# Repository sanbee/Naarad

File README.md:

# Naarad
A simple house monitor and control system. 

The *Naarad* system is a network of remote Nodes with a radio operating
in the [ISM band](https://en.wikipedia.org/wiki/ISM_band) and a Base
Station with an [RFM69CW](http://www.hoperf.com/rf_transceiver/modules/RFM69CW.html) (RFM) packet radio, currently connected to an
Arduino UNO.  The UNO talks to a Linux-based computer (currently a
Raspberry PI (RPi)) via the serial connection.  The RPi also listens
for incoming socket connections.  Commands for the *Naarad* network
are either generated at the RPi or arrive at the socket (e.g. from a
remotely connected device).  Commands meant for the UNO or the remote
Nodes are sent to the UNO via the serial connection.  The server on
the UNO then transmits the commands for the remote Nodes via the RFM
or via another radio for remote [OOK](https://en.wikipedia.org/wiki/On-off_keying)
devices.  Similarly, information from remote Nodes is received at the 
UNO via the RFM and immediately transferred to the RPi for consumption 
via the serial connection. The block level system diagram looks like this:

This repository has the code for the three components of the Naarad system: 
  * The code running on the MCUs on the remote nodes is in the [Nodes](Nodes) directory
  * The code running on the Arduino UNO on the Base Station is in the [BaseStation](BaseStation) directory
  * The code running on the central socket server (Raspberry Pi) is in the [RPi](RPi) directory

### Resources
The communication with the RFM is done using the
[JeeLib](https://github.com/jcw/jeelib) library from
[JeeLabs](https://jeelabs.org).

The communication hardware on the remote Nodes is derived from the
[TinyTx](https://nathan.chantrell.net/tinytx-wireless-sensor) design.
For programming the ATTiny84 using an Arduino, I followed the
instructions from [here](https://nathan.chantrell.net/20120225/an-attiny-based-wireless-temperature-sensor/).

[This](http://www.gammon.com.au/power) article by [Nick Gammon](http://www.gammon.com.au/forum/bbshowbio.php?bbuser_id=1) is an excellent resource for techniques to reduce power consumption on MCU. While the code here is for Arduino (Atmega328P), some of the techniques apply to other Atmel processors.  A similar article sepecifically for ATTiny84 would be great.  This also has a post with very useful information about batteries (including self-drainage rates etc.).

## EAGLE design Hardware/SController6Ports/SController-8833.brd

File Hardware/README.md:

# Naarad Hardware

|  Prototype | Version 1 |
| :---:     | :---:   |
|   |   |

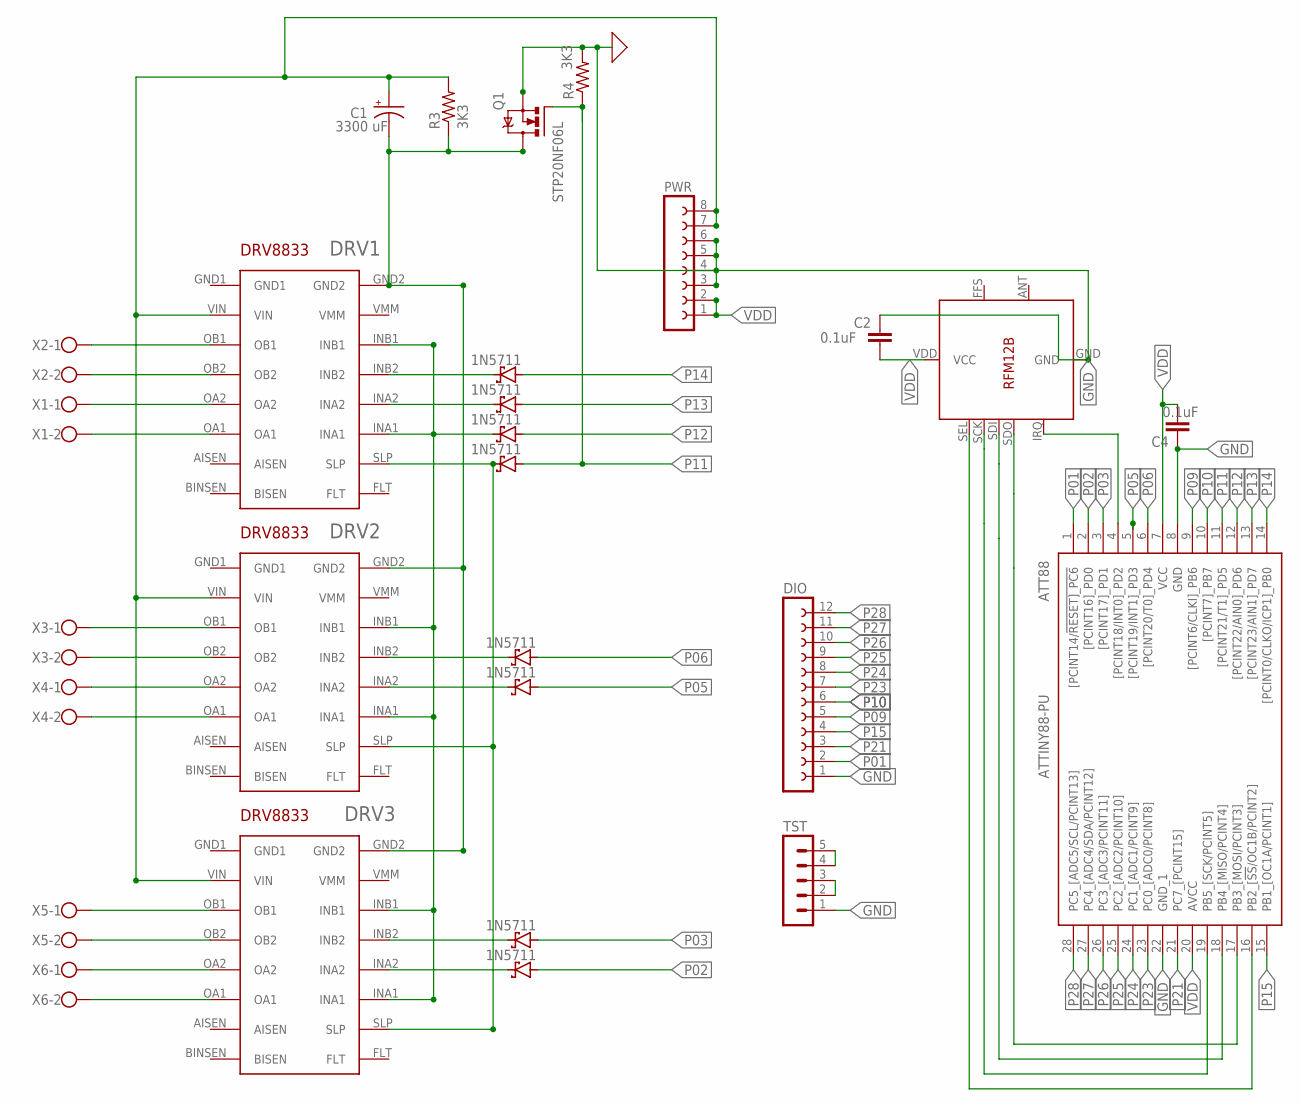
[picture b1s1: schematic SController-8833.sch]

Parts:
1: DRV1; POLOLU-DRV8833
2: DRV2; POLOLU-DRV8833
3: DRV3; POLOLU-DRV8833
ATT88: ATTINY88-PU; DIP794W53P254L3467H457Q28N
C1: 3300 uF; E5-10,5
C2, C4: 0.1uF; C2.5-2
D1, D2, D3, D4, D5, D6, D7, D8: 1N5711; F126Z12
DIO: FE12-1; FE12
PWR: FE08-1; FE08
Q1: STP20NF06L; TO220BV
R3, R4: 3K3; 0204/7
RFM69CW: RFM69CW; RFM12B
TST: MA05-1
X1, X2, X3, X4, X5, X6: W237-102

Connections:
CMN1: 1.INA1, 1.INB1, 2.INA1, 2.INB1, 3.INA1, 3.INB1, D3.C
GND: ATT88.8 (GND), ATT88.22 (GND_1), C2.2, C4.1, DIO.1, PWR.3, PWR.4, PWR.5, PWR.6, Q1.S, R4.2, RFM69CW.GND, TST.1
IRQ: ATT88.4 ([PCINT18/INT0]_PD2), RFM69CW.IRQ
unnamed: 2.INB2, D5.C
unnamed: 1.INB2, D1.C
unnamed: TST.4, TST.5
unnamed: TST.2, TST.3
unnamed: 1.INA2, D2.C
unnamed: 3.INB2, D7.C
unnamed: 2.INA2, D6.C
unnamed: 3.INA2, D8.C
OA11: 1.OA1, X1.2
OA12: 2.OA1, X4.2
OA13: 3.OA1, X6.2
OA21: 1.OA2, X1.1
OA22: 2.OA2, X4.1
OA23: 3.OA2, X6.1
OB11: 1.OB1, X2.1
OB12: 2.OB1, X3.1
OB13: 3.OB1, X5.1
OB21: 1.OB2, X2.2
OB22: 2.OB2, X3.2
OB23: 3.OB2, X5.2
P01: ATT88.1 ([PCINT14/!RESET]_PC6), DIO.2
P02: ATT88.2 ([PCINT16]_PD0), D8.A
P03: ATT88.3 ([PCINT17]_PD1), D7.A
P05: ATT88.5 ([PCINT19/INT1]_PD3), D6.A
P06: ATT88.6 ([PCINT20/T0]_PD4), D5.A
P09: ATT88.9 ([PCINT6/CLKI]_PB6), DIO.5
P10: ATT88.10 ([PCINT7]_PB7), DIO.6
P11: ATT88.11 ([PCINT21/T1]_PD5), D4.A, Q1.G, R4.1
P12: ATT88.12 ([PCINT22/AIN0]_PD6), D3.A
P13: ATT88.13 ([PCINT23/AIN1]_PD7), D2.A
P14: ATT88.14 ([PCINT0/CLKO/ICP1]_PB0), D1.A
P15: ATT88.15 (PB1_[OC1A/PCINT1]), DIO.4
P21: ATT88.21 (PC7_[PCINT15]), DIO.3
P23: ATT88.23 (PC0_[ADC0/PCINT8]), DIO.7
P24: ATT88.24 (PC1_[ADC1/PCINT9]), DIO.8
P25: ATT88.25 (PC2_[ADC2/PCINT10]), DIO.9
P26: ATT88.26 (PC3_[ADC3/PCINT11]), DIO.10
P27: ATT88.27 (PC4_[ADC4/SDA/PCINT12]), DIO.11
P28: ATT88.28 (PC5_[ADC5/SCL/PCINT13]), DIO.12
SCK: ATT88.19 (PB5_[SCK/PCINT5]), RFM69CW.SCK
SDI: ATT88.18 (PB4_[MISO/PCINT4]), RFM69CW.SDI
SDO: ATT88.17 (PB3_[MOSI/PCINT3]), RFM69CW.SDO
SEL: ATT88.16 (PB2_[!SS!/OC1B/PCINT2]), RFM69CW.SEL
SLP: 1.SLP, 2.SLP, 3.SLP, D4.C
VDD: ATT88.7 (VCC), ATT88.20 (AVCC), C2.1, C4.2, PWR.1, PWR.2, RFM69CW.VDD (VCC)
VGND: 1.GND2, 2.GND2, 3.GND2, C1.-, Q1.D, R3.1
VIN: 1.VIN, 2.VIN, 3.VIN, C1.+, PWR.7, PWR.8, R3.2

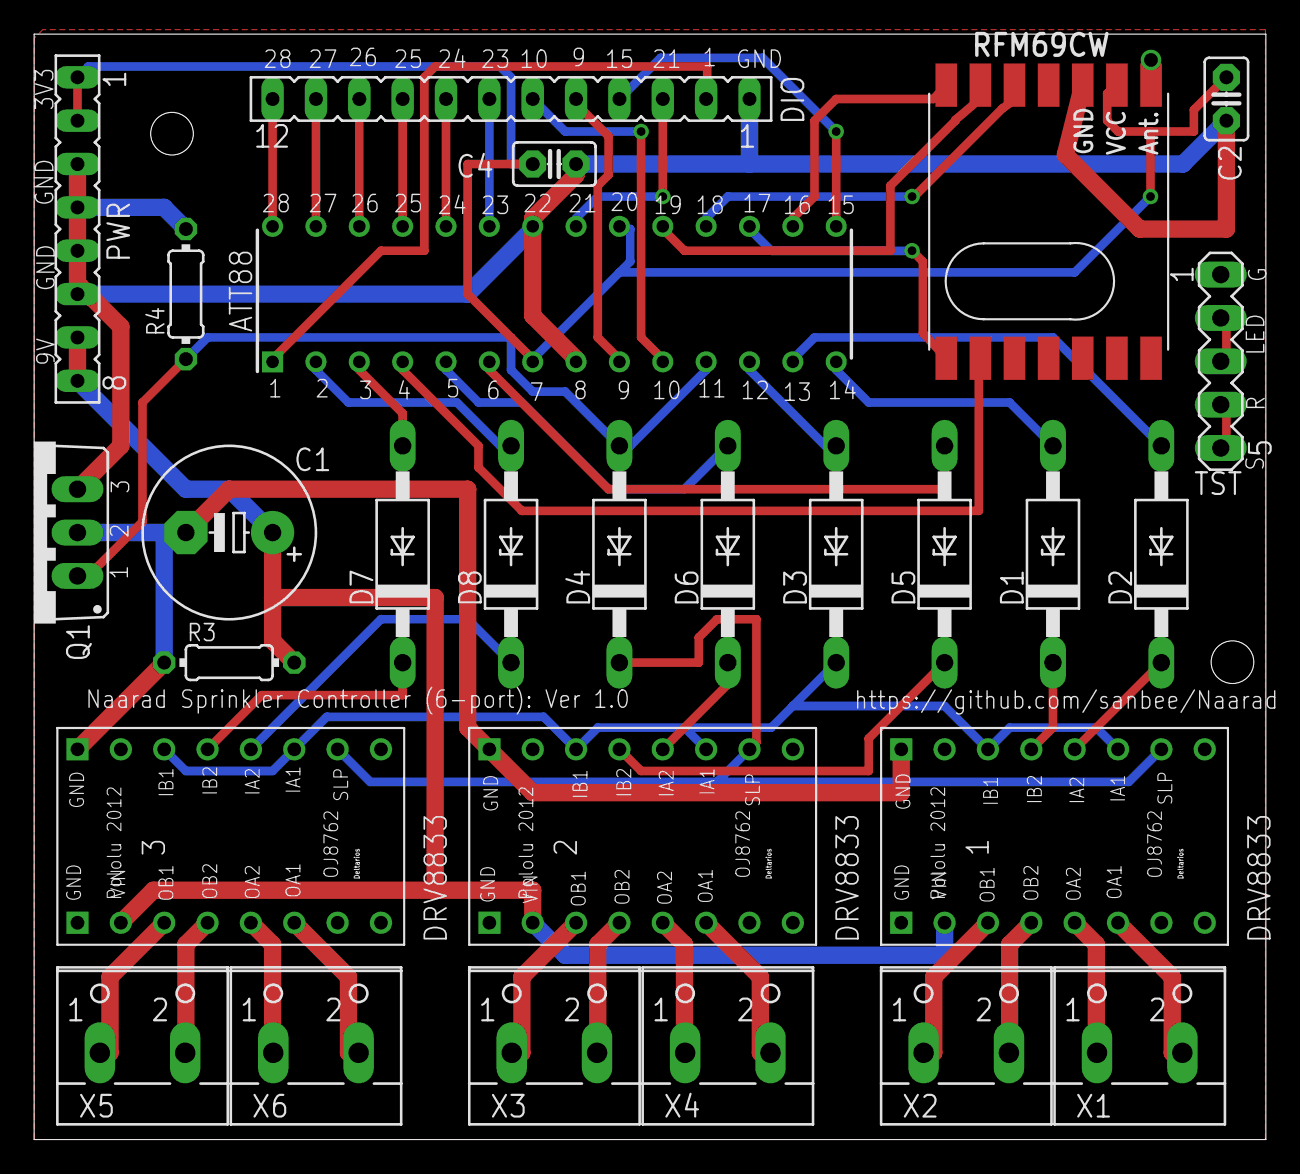
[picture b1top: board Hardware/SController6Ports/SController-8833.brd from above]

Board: 2 copper layers, 72.2 x 64.8 mm, 28 parts (0 on the bottom side), 50 nets.

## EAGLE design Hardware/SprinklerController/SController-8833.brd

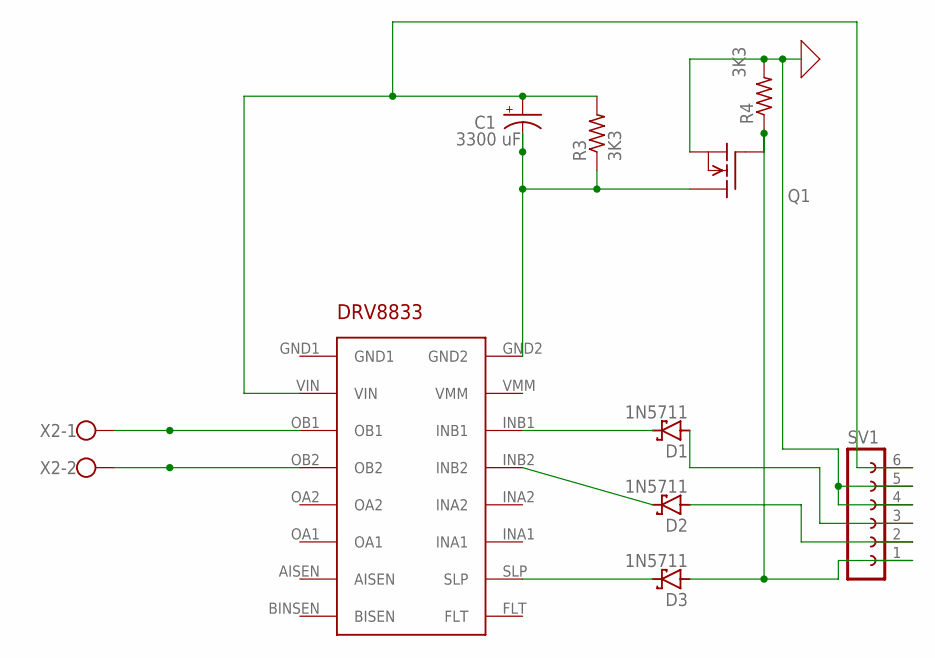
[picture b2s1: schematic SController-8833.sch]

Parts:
"": POLOLU-DRV8833
C1: 3300 uF; E5-10,5
D1, D2, D3: 1N5711; F126Z12
Q1: SUP75N06-08; TO220
R3: 3K3; 0204/7
R4: R-US_0204/7; 0204/7
SV1: FE06-1; FE06
X2: W237-102

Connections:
0: Q1.3 (S), R4.2, SV1.4, SV1.5
unnamed: "".INB1, D1.C
unnamed: "".INB2, D2.C
unnamed: "".SLP, D3.C
unnamed: "".VIN, C1.+, R3.2, SV1.6
unnamed: "".GND2, C1.-, Q1.2 (D), R3.1
unnamed: "".OB1, X2.1
unnamed: D3.A, Q1.1 (G), R4.1, SV1.1
unnamed: D2.A, SV1.2
unnamed: "".OB2, X2.2
unnamed: D1.A, SV1.3

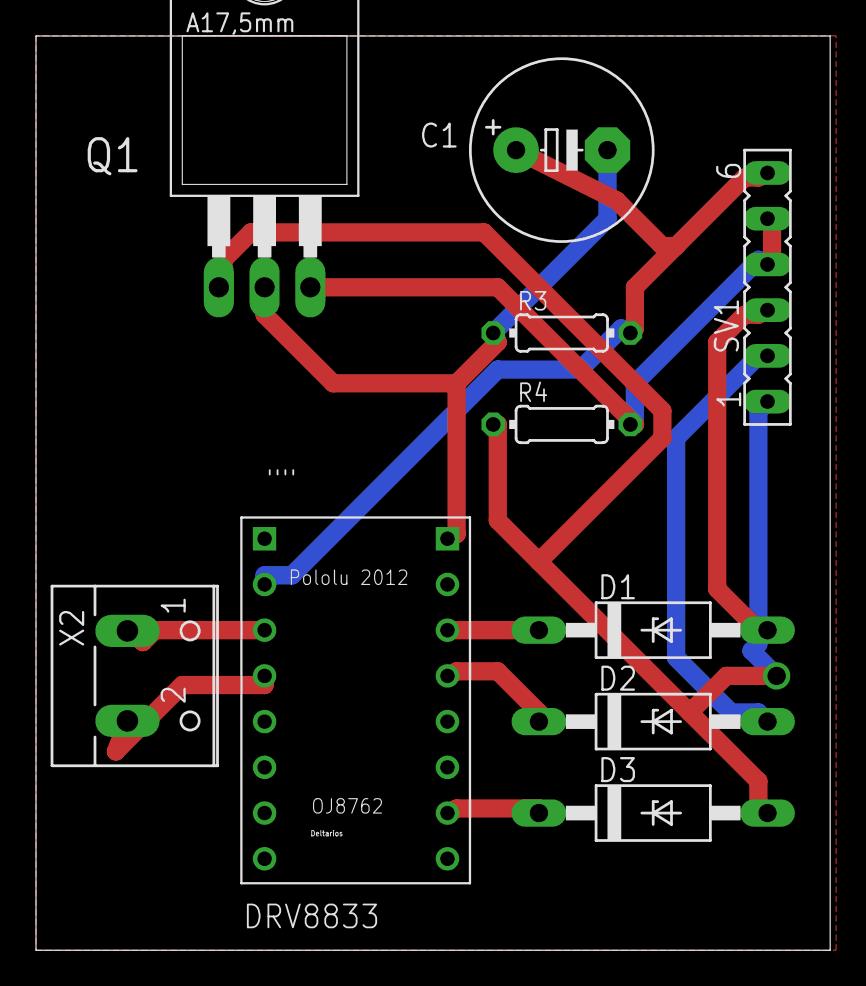
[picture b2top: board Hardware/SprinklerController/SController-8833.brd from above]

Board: 2 copper layers, 44.1 x 50.8 mm, 10 parts (0 on the bottom side), 11 nets.

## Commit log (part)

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2018-02-15 First commit to GitHub
2018-02-16 Adding test owm code
2018-02-16 Typo corrections
2018-02-21 Adding docs dir. to collect docs in one place.
2018-03-14 Code cleanup.
    readRFM69() is now run-time efficient and more readable.
2018-03-17 Cleaned-up the python apps.
    Load the mysockect module from NaaradServer + made them exectuable commandline commands.Z
2018-03-20 Minor changes in README.md
2018-03-29 Listener node list is N_LISTENERS long.
2018-04-07 Inital multiport sprinkler controller code
2018-04-09 Ini A0-3,A7,B0 to LOW+gne. 10ms pulse for OPEN/CLOSE cmd.
2018-04-17 Mods to make each listener truly indep. at the server.
    Holds separate counters and TX_payloads for each listener.
2018-04-19 Set node ID in INIT_TXPKT.
2018-04-23 Catch for out of range nodeID in SEND_RFM command tested to work.
    Previous commit had an error in the constructed error message as a
    JSON string.
2018-05-13 Un-formated the ATT84 pin-layout diagram
2018-06-27 DRV8838Tst: Changed pin names to EN and PH to match names on the chip docs. RFM69_RxTx: Explicitly shut the radio at the end of each loop().
2018-06-30 Tested to draw 20uAmp in the sleep mode.
2018-07-06 Set the default timeout value to 10sec.
2018-07-10 Added test ON-OFF cycle in setup() to decouple debugging h/w vs. s/w
    Enable the ADCs at the beginning of loop() and disable at the end just
    before putting MCU to deep-sleep.
2018-07-18 Script for SEND_CMD to use send-ack protocol.
    Still in the making...
2018-07-22 Adds sets *any* packet to the gCurrentPacket array (per node).
    Earlier, only packets with rf_fail=0 were added. This change
    essentially also add the ACKpkt, which arrive with rf_fail=1 since
    they don't carry sensory data and only ACK of the commands exectued at
    the listener nodes.
2019-01-11 poll.py is experimental. sprinkler.cmd has the seq. of commands that work.
2019-01-19 Added -B option for the screen command
2019-01-25 Non simulation version of the code from CmdQSim branch for deployment.
2019-01-31 Removed non-app files from RPi/Apps
2019-02-03 Removed include <QueueArray.h>
2019-02-05 Minor improvements in the system software arch. design diagram.
2019-02-10 Hopefully a thread-safe version with multiple client threads registered with the main thread.
2019-02-12 Look for a listener-node packet before issuing a NaaradNotify.
2019-02-12 Changing symlink to a physical file BaseStation/unoserver2/RemoteCmd.h
2019-02-14 Adding explanatory comments.
2019-02-16 Removed ' ' in the accumulation of chunk0.
2019-02-16 Program to test ClientList
2019-02-19 Bug fix in notify.py
2019-02-19 Command to convert PDF to hires PNG.
2019-02-20 Bug fixes in NaaradUtils.
2019-02-21 naaradboot version that uses software from GitHub repos.
2019-02-23 mySock: Code cleanup+more robust send/receive. notify.py does a blocking receive call.
2019-02-25 Doing a raw (not robust) initial sock.recv(16), as earlier. This works with aNaarad app. Needs more work to make getNChar() work for the initial read, which makes receive() robust.
2019-03-07 Send Open command twice. The second one works. The first never works. Don't know why.
2019-03-29 Typo corrections in the comments.
2019-05-20 Untested re-factored code in myClientThread5.py
    Breaking up the event loop into classing functions for commands that
    takes non-trivial code to handle the command.
2019-05-20 Removed hLenght from NaaradTopics2 (not required) and moved it to settings5 (the global settings object).
2019-05-22 Added NAARAD_SHUTDOWN flag in settings5.py and used in naaradsim and NaaradTopicSim.
2019-05-22 Added settings5.NAARAD_SHUTDOWN flag and used in naarad.py and NaaradTopics2.py.
    The "shutdown" command issued twice will shut both server threads. The server process
    itself will stop thereafter.
2019-05-23 Added message when the threads exit based on NAARAD_SHUTDOWN flag.
2019-05-25 messageHandler() returns a bool to indicate if the event loop should end.
    "done" is the only command that ends the event loop and the thread terminates.
2019-05-25 Adding sendcmd and serverinfo. Latter is used to get server name and port.
2019-05-28 Added "source" field in the info. JSON string.
2019-05-29 De-register the client associated with this thread before exiting handleContNotify().
2019-05-30 Better handling of exceptions throw from abortContNotify+cosmetic changes in error strings.
2019-06-02 serverinfo: Setting default SERVER to "naaradhost" settings5: Setting history time-length to 2*24hr.
2019-06-05 Add time stamp to the packet (JSON string) only if "rf_fail" key is found.
2019-06-13 Schematic and TxT version of connections between RFM69 and Arduino UNO.
2019-06-25 Typo error in except object fixed!
2019-06-27 Removed client control on comPort.open() .close().
    comPort's open/close are now internally managed, as it should be.
    myClTh: No uno.open()/.close() calls are made anywhere.
    comPort.py: Increment/decrement of users is internally protected by Lock.
    The "RFM_SEND" and "tell" commands were using uno.open()/close(). Now disabled.
    the "open" and "close" commands now only print a message.
    App/cmdnaard: Added a comment.
2019-07-10 NaaradUtils: Added addKey() function. This handles non-JSON strings gracefully. NaaradTopic2: Using Utils.addKey() to add "cmd":-1 in packets that don't have "cmd". NaaradTopicSim: Same changes as in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
2019-07-10 Processes packets with rf_fail=0 also for notification.
2019-07-14 Fixed the path to the sys. diagram.
2019-07-14 A smaller PNG file.
2019-07-14 Readme for h/w
2019-07-15 Tiny PCB PNG (loads faster).
2019-07-24 This checkin was tested to get around the JeeLib bug due to which the radio freezes after ~2days of operation. unoserver2: Reset RFM69 if the time of last recvd pkt > 10sec. This reset is a workaroun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
2019-08-04 Commiting conflict resolution in cmdnaarad.py.
2019-08-10 First version with setSolenoidPort() function compiled. Not tested yet.
2019-08-11 Added strftime() to log messages.
2019-08-11 Corrected mask for DRV port 4. Using #defines for all masks for more readable code.
2019-08-13 Marked pins not used for port control as ('?' for PIN2 and 'S' for PIN5 (used for SLP on DRV)).
2019-08-15 Shut all pots in setup().
2019-08-19 Made the comments more accurate (for future reference).
2019-09-05 Working version of ATTiny88Pins.h and .ino. This code was tested on the actual sprinklers. Will clean-up the code and bring in the code needed for radio communication after this checkin.
2019-09-23 Add: Added info. about ATT88<-->RFM connection on SC6Port V1 PCB. Conclusion is that all's OK on the SC6 V1 PCB.
2019-09-27 Fix: Input argument (named argv) was ignored. sys.argv was used instead in cmdnaarad.py and notfiy.py Chg: Changed the function name from main() to cmdnaarad().
2019-09-30 Chg: Fixed markdown formatting
2019-10-01 Add: README.md in SC6Port with info. about RFM69-ATT88 and ATT88-UNO connections.
2019-10-02 Chg: This code works with ATT88 and RFM69 on breadboard. The timing to get regular pings and ACK packets seems quite fragile -- don't know why.
    Every line of code in the loop() function is same as that works on ATT84/RFM69. They
    are also called in exact same sequence, and both -- the exact lines of code and
    their sequence seems to be critical. This suggestes that timing (delays) for the
    radio operations needs to be better understood.
2019-10-07 Add: Initialize the RFM in every loop(). This gives most consistent ping-pong.
2019-10-10 This is a full working version before. Code cleanup will be after this check-in. Add: Code at the top of the setup() function to run ATT88 at 4MHz (the minimum clock speed required by RFM69CW using J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
2019-10-14 Chg: Cleaned-up code check in. All of the commented test-code has been deleted. The commit immediately previous has the test code, with the active code as as in this commit.
2019-10-28 Some typo corrections+clarifications in README.md
2019-12-02 Chg: Using A5 as the pin to read local temperature (TMP36).
    This is the configuration on the new naaradhost.
2019-12-03 Chg: Changed node ID from 15 to 17.
2020-05-10 Leaving in a comment.
2020-05-22 Add: Adding the Queue library code used in BaseStation Arduino code. Add: NaaradSoftware.pdf, 6Ports/Schematic.pdf Add: App/sprinkler*.{cmd,py,sh} Add: Simulator/notify.py
2020-05-26 Fix: Option for sleep is $t0 (instead of t0).
2020-06-22 Chg: lightOn.py: using arg passed to the function instread of sys.argv sprinkler_cmd_6port.sh: Minor cosmetic changes.
2020-06-24 Chg: cnotify.py: Minor changes + convert time from seconds to asctime Chg: Changed use of sys.argv to argv in function cnotify(). Chg: Changed the name from notify() to cnotify().
2020-06-30 Chg: Changed print statements that work with Py2 and Py3. mySock.py: An accumulator variable for bytes is initialized as bytearray().
2020-07-23 Chg: mySock::receive() now catches KeyboardInterrupt and raise it again with a message. Chg: cnotify.py catches interrupt exception and exits cleanly.
2021-03-29 Added a comment to remind that there is a possible bug in mySock.py::getNChar() due to which this script does not execute on the server if the long comment at the beginning is included.
2021-03-29 Removed printing the script on the screen.
2023-06-21 Added "untracked" files, some of which looked useful. Adding Eagle_Libraries_As_Submodule as submodule.
2024-07-15 Added documentation for NaaradNotify() function in NaaradServer/NewServer/ClientList.py
2024-08-08 Using python3 as the shell + converted print statements to Py3
2025-01-26 Moved NaaradServer to lib/NaaradServer. Added Apps/naaradpath.py to add paths to load Naarad modules. All Naarad apps that need Naarad modules need to import this naaradpath.py.
2025-07-19 Adding rbootnaarad.sh script for rebooting remotely. Added light-0 on at 6AM on weekdays to sunwait.crontab
2025-08-09 Capability to self reboot.
    Self-reboot is now initiated if uno.readline() returns a blank string
    which is supposed to indicate COM port read-timeout. When this is
    detected, send the shutdown command twice on localpost socket 1234.
    With this the sever shutsdown and initServer() call in naarad.py
    exits, allowing a reboot sequence to begin.
    In naarad.py __main__, rapid reboots (reboots within 1 min of each
2025-08-18 Minor improvements in NaaradTopic2.py and naarad.py NaaradTopic2.py: The shutdown() function takes a boolean. Added a newline to the message written to /tmp/naarad_reboot.log
    naarad.py: Cleanup
2025-08-19 Added the deprecation notice in the following files: NaaradTopicSim.py comPortSim.py naaradsim.py
2025-08-28 NewServer/comPort.py: Actually close the port if count <= 0 NewServer/naarad.py: Return uno and pogo from initServer() and issue uno.close() as part of reboot sequence. Simulator/comPort.py: Improved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
2025-09-09 Renamed tt -> sprinkler.tt
2025-09-10 readjson.py: Experimental to read JSON packets from stdin. In a pipe, this does not work when the input is from a live server. Don't know why.
2025-09-15 Addeding examples dir. with example code, for a Python based Naarad app.
    bokeh_server_naarad.py has a working framework that injest data from
    a live Naarad server (via cnotify()). The callback pipes seem to be
    connected, but the data is not yet plotted.
